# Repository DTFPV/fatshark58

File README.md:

fatshark58
==========

A PCB design in eagle to use other 5.8GHz receiver modules on Fatshark googles

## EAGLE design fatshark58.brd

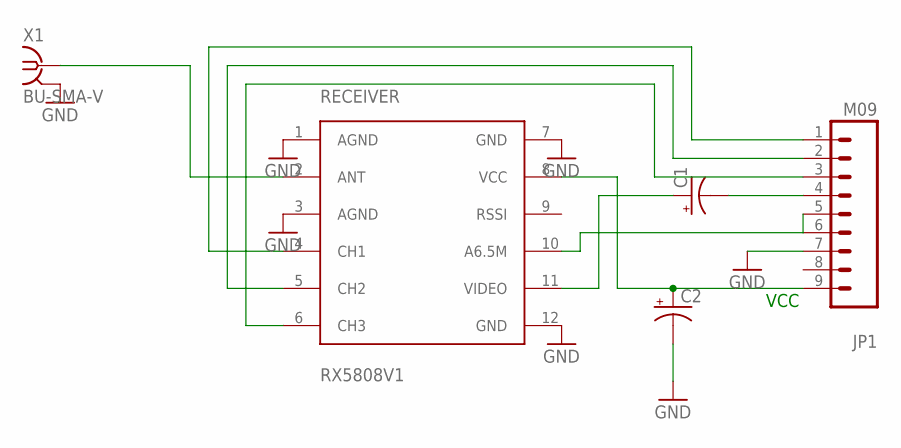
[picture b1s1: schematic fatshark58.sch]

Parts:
C1, C2: CAP_POL7343; EIA7343
JP1: M09; 1X09
RECEIVER: RX5808V1; RX5808
X1: BU-SMA-V

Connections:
GND: C2.C (-), JP1.7, RECEIVER.1 (AGND), RECEIVER.3 (AGND), RECEIVER.7 (GND), RECEIVER.12 (GND), X1.2, X1.3 (2), X1.4 (2), X1.5 (2)
unnamed: JP1.3, RECEIVER.6 (CH3)
unnamed: C1.A (+), RECEIVER.11 (VIDEO)
unnamed: JP1.1, RECEIVER.4 (CH1)
unnamed: JP1.2, RECEIVER.5 (CH2)
unnamed: C2.A (+), JP1.9, RECEIVER.8 (VCC)
unnamed: JP1.5, JP1.6, RECEIVER.10 (A6.5M)
unnamed: C1.C (-), JP1.4
unnamed: RECEIVER.2 (ANT), X1.1

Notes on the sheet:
VCC

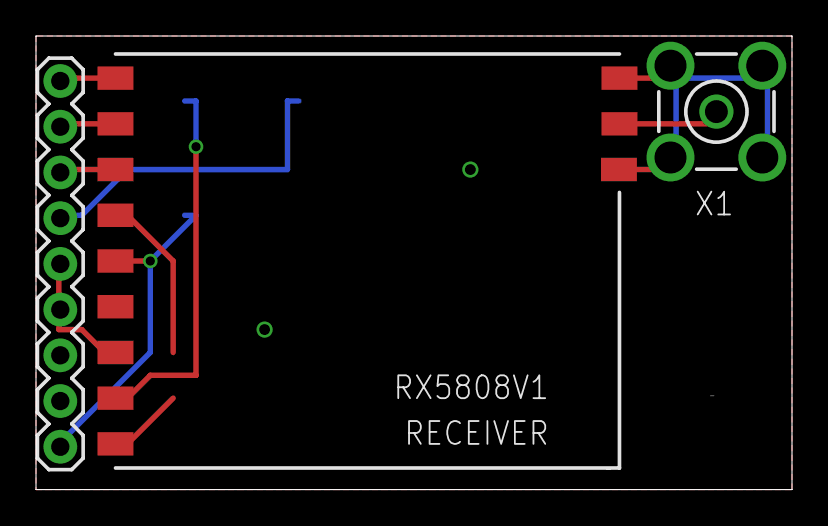
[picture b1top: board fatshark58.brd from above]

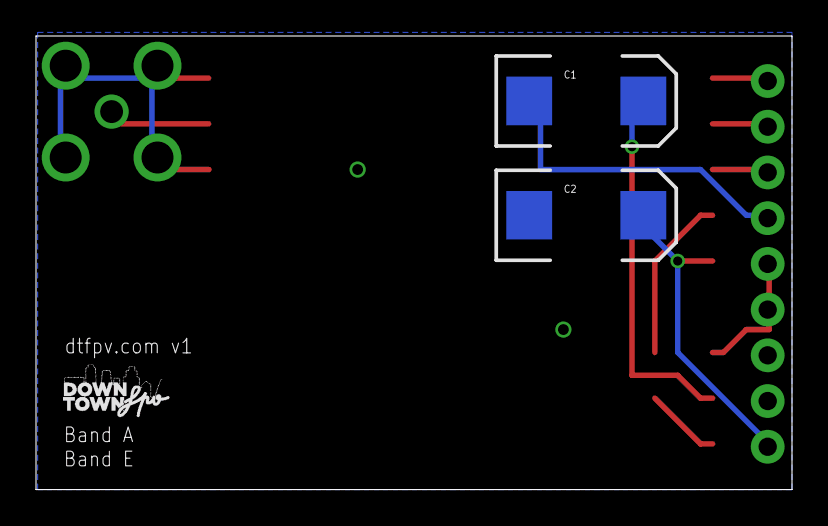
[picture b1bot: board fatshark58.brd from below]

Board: 2 copper layers, 42.0 x 25.2 mm, 5 parts (2 on the bottom side), 9 nets.

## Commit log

2014-02-26 V1 of the PCB

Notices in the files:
parts and their libraries:
SparkFun-Connectors: Licensing: CC v3.0 Share-Alike You are welcome to use this library for commercial purposes.
